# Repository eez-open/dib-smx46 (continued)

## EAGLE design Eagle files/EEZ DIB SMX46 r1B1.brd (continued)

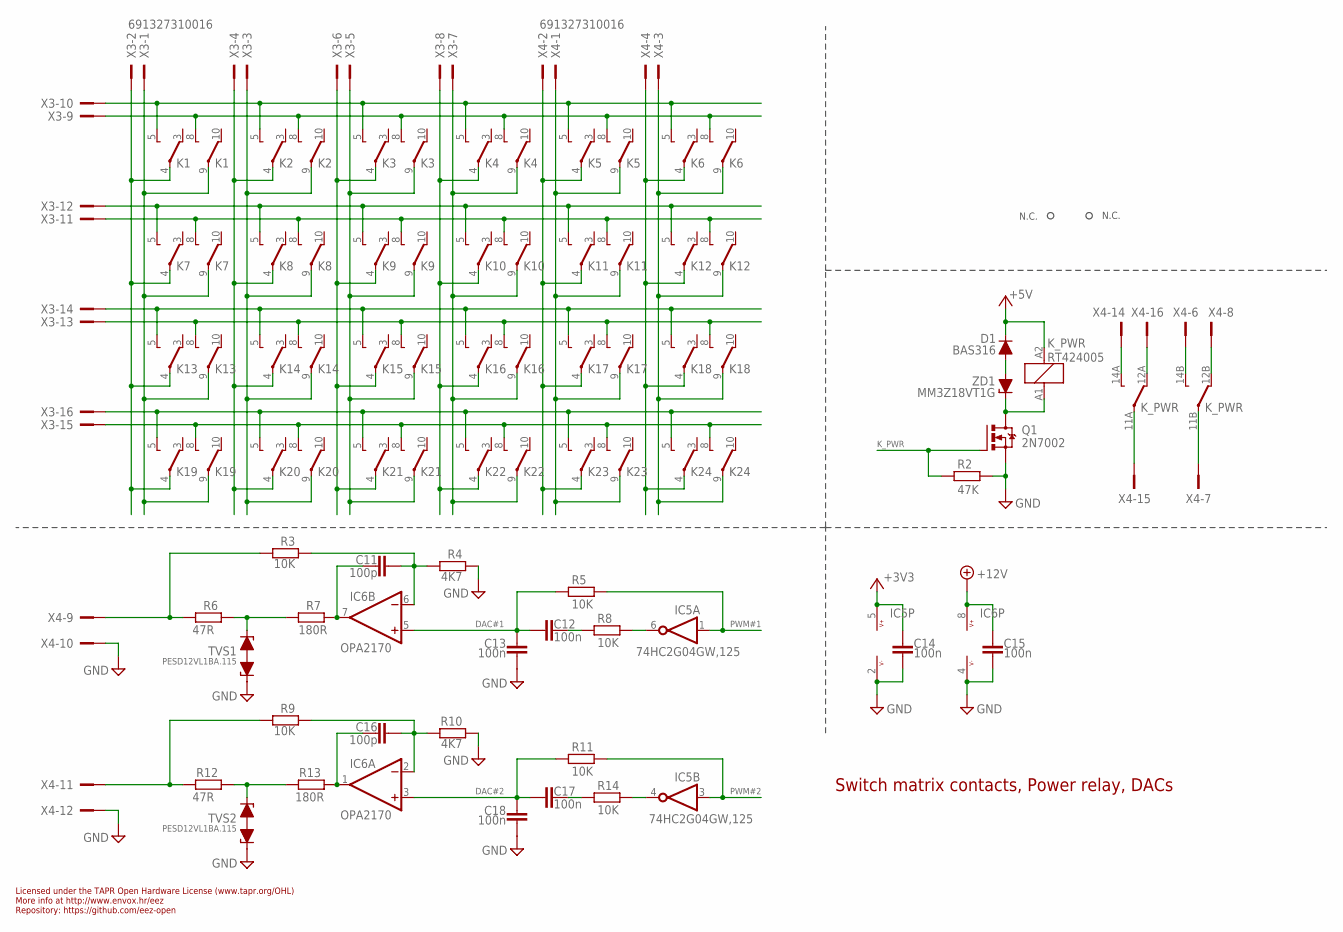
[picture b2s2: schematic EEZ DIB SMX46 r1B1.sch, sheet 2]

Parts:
C11, C16: 100p; C0805
C12, C13, C14, C15, C17, C18: 100n; C0603
D1: BAS316; SOD323-R
IC5: 74HC2G04GW,125; SOT65P210X110-6N
IC6: OPA2170; SOIC127P600X173-8N
K1, K2, K3, K4, K5, K6, K7, K8, K9, K10, K11, K12, K13, K14, K15, K16, K17, K18, K19, K20, K21, K22, K23, K24: FTR-C1GA012G-B05; FTR-C1
K_PWR: RT424005; RT-C/016A5_ROUND
Q1: 2N7002; SOT103P240X110-3N; MPN 2N7002-7-F
R2: 47K; R0805
R3, R5, R8, R9, R11, R14: 10K; R0805
R4, R10: 4K7; R0805
R6, R12: 47R; R0805
R7, R13: 180R; R0805
TVS1, TVS2: PESD12VL1BA.115; SOD323-BIDIR
X3, X4: 691327310016
ZD1: MM3Z18VT1G; SOD323-R

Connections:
+3V3: C14.1, IC5.5 (V+); also elsewhere on the board
+5V: D1.C, K_PWR.A2 (C1); also elsewhere on the board
+12V: C15.1, IC6.8 (V+); also elsewhere on the board
DAC#1: C12.1, C13.1, IC6.5 (+IN), R5.1
DAC#2: C17.1, C18.1, IC6.3 (+IN), R11.1
GND: C13.2, C14.2, C15.2, C18.2, IC5.2 (V-), IC6.4 (V-), Q1.2 (S), R2.1, R4.1, R10.1, TVS1.1, TVS2.1, X4.10, X4.12; also elsewhere on the board
ISET1: R6.1, R7.2, TVS1.2
ISET2: R12.1, R13.2, TVS2.2
K_PWR: Q1.1 (G), R2.2; also elsewhere on the board
unnamed: K1.4, K7.4, K13.4, K19.4, X3.2
unnamed: K1.9, K7.9, K13.9, K19.9, X3.1
unnamed: K13.5 (O), K14.5 (O), K15.5 (O), K16.5 (O), K17.5 (O), K18.5 (O), X3.14
unnamed: K13.8 (O), K14.8 (O), K15.8 (O), K16.8 (O), K17.8 (O), K18.8 (O), X3.13
unnamed: K7.5 (O), K8.5 (O), K9.5 (O), K10.5 (O), K11.5 (O), K12.5 (O), X3.12
unnamed: K7.8 (O), K8.8 (O), K9.8 (O), K10.8 (O), K11.8 (O), K12.8 (O), X3.11
unnamed: K19.5 (O), K20.5 (O), K21.5 (O), K22.5 (O), K23.5 (O), K24.5 (O), X3.16
unnamed: K19.8 (O), K20.8 (O), K21.8 (O), K22.8 (O), K23.8 (O), K24.8 (O), X3.15
unnamed: K5.4, K11.4, K17.4, K23.4, X4.2
unnamed: K2.4, K8.4, K14.4, K20.4, X3.4
unnamed: K2.9, K8.9, K14.9, K20.9, X3.3
unnamed: K5.9, K11.9, K17.9, K23.9, X4.1
unnamed: K6.4, K12.4, K18.4, K24.4, X4.4
unnamed: K6.9, K12.9, K18.9, K24.9, X4.3
unnamed: K3.4, K9.4, K15.4, K21.4, X3.6
unnamed: K3.9, K9.9, K15.9, K21.9, X3.5
unnamed: K4.4, K10.4, K16.4, K22.4, X3.8
unnamed: K4.9, K10.9, K16.9, K22.9, X3.7
unnamed: R3.2, R6.2, X4.9
unnamed: C17.2, R14.1
unnamed: IC5.4 (O), R14.2
unnamed: C11.1, IC6.7 (OUT), R7.1
unnamed: C16.2, IC6.2 (-IN), R9.1, R10.2
unnamed: C16.1, IC6.1 (OUT), R13.1
unnamed: K1.5 (O), K2.5 (O), K3.5 (O), K4.5 (O), K5.5 (O), K6.5 (O), X3.10
unnamed: K1.8 (O), K2.8 (O), K3.8 (O), K4.8 (O), K5.8 (O), K6.8 (O), X3.9
unnamed: K_PWR.11B, X4.7
unnamed: K_PWR.12B (S), X4.8
unnamed: R9.2, R12.2, X4.11
unnamed: K_PWR.14B (O), X4.6
unnamed: K_PWR.11A, X4.15
unnamed: K_PWR.12A (S), X4.16
unnamed: K_PWR.14A (O), X4.14
unnamed: D1.A, ZD1.A
unnamed: K_PWR.A1 (C2), Q1.3 (D), ZD1.C
unnamed: C12.2, R8.1
unnamed: C11.2, IC6.6 (-IN), R3.1, R4.2
unnamed: IC5.6 (O), R8.2
PWM#1: IC5.1 (I), R5.2; also elsewhere on the board
PWM#2: IC5.3 (I), R11.2; also elsewhere on the board

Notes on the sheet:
Licensed under the TAPR Open Hardware License (www.tapr.org/OHL)
Repository: https://github.com/eez-open
More info at http://www.envox.hr/eez
Switch matrix contacts, Power relay, DACs
N.C.

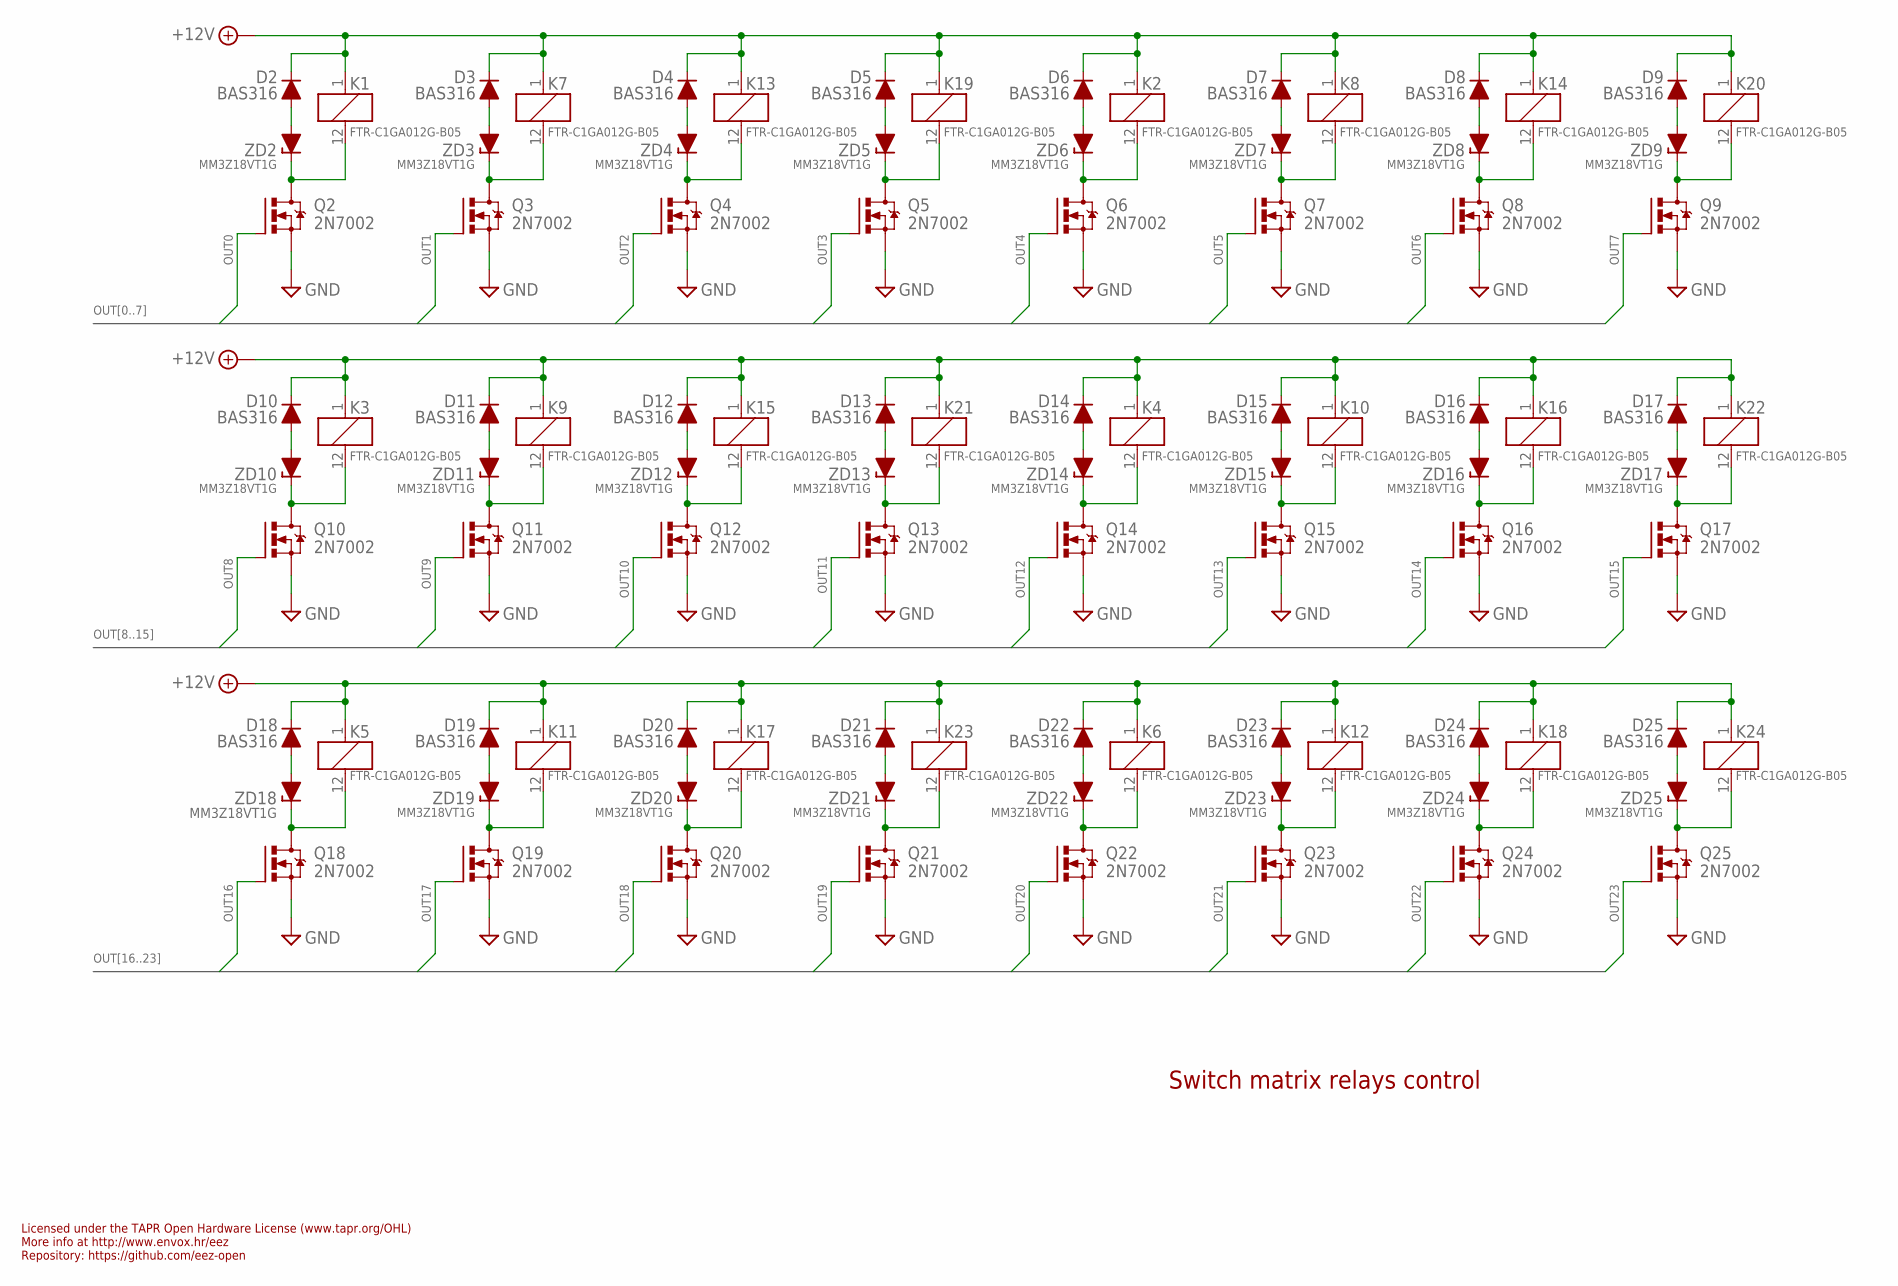
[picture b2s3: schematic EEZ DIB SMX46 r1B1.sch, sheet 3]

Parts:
D2, D3, D4, D5, D6, D7, D8, D9, D10, D11, D12, D13, D14, D15, D16, D17, D18, D19, D20, D21, D22, D23, D24, D25: BAS316; SOD323-R
K1, K2, K3, K4, K5, K6, K7, K8, K9, K10, K11, K12, K13, K14, K15, K16, K17, K18, K19, K20, K21, K22, K23, K24: FTR-C1GA012G-B05; FTR-C1
Q2, Q3, Q4, Q5, Q6, Q7, Q8, Q9, Q10, Q11, Q12, Q13, Q14, Q15, Q16, Q17, Q18, Q19, Q20, Q21, Q22, Q23, Q24, Q25: 2N7002; SOT103P240X110-3N; MPN 2N7002-7-F
ZD2, ZD3, ZD4, ZD5, ZD6, ZD7, ZD8, ZD9, ZD10, ZD11, ZD12, ZD13, ZD14, ZD15, ZD16, ZD17, ZD18, ZD19, ZD20, ZD21, ZD22, ZD23, ZD24, ZD25: MM3Z18VT1G; SOD323-R

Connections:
+12V: D2.C, D3.C, D4.C, D5.C, D6.C, D7.C, D8.C, D9.C, D10.C, D11.C, D12.C, D13.C, D14.C, D15.C, D16.C, D17.C, D18.C, D19.C, D20.C, D21.C, D22.C, D23.C, D24.C, D25.C, K1.1 (C1), K2.1 (C1), K3.1 (C1), K4.1 (C1), K5.1 (C1), K6.1 (C1), K7.1 (C1), K8.1 (C1), K9.1 (C1), K10.1 (C1), K11.1 (C1), K12.1 (C1), K13.1 (C1), K14.1 (C1), K15.1 (C1), K16.1 (C1), K17.1 (C1), K18.1 (C1), K19.1 (C1), K20.1 (C1), K21.1 (C1), K22.1 (C1), K23.1 (C1), K24.1 (C1); also elsewhere on the board
GND: Q2.2 (S), Q3.2 (S), Q4.2 (S), Q5.2 (S), Q6.2 (S), Q7.2 (S), Q8.2 (S), Q9.2 (S), Q10.2 (S), Q11.2 (S), Q12.2 (S), Q13.2 (S), Q14.2 (S), Q15.2 (S), Q16.2 (S), Q17.2 (S), Q18.2 (S), Q19.2 (S), Q20.2 (S), Q21.2 (S), Q22.2 (S), Q23.2 (S), Q24.2 (S), Q25.2 (S); also elsewhere on the board
unnamed: D4.A, ZD4.A
unnamed: K13.12 (C2), Q4.3 (D), ZD4.C
unnamed: D10.A, ZD10.A
unnamed: D8.A, ZD8.A
unnamed: K14.12 (C2), Q8.3 (D), ZD8.C
unnamed: K3.12 (C2), Q10.3 (D), ZD10.C
unnamed: D9.A, ZD9.A
unnamed: K20.12 (C2), Q9.3 (D), ZD9.C
unnamed: D11.A, ZD11.A
unnamed: K9.12 (C2), Q11.3 (D), ZD11.C
unnamed: D7.A, ZD7.A
unnamed: K8.12 (C2), Q7.3 (D), ZD7.C
unnamed: D12.A, ZD12.A
unnamed: K15.12 (C2), Q12.3 (D), ZD12.C
unnamed: D6.A, ZD6.A
unnamed: K2.12 (C2), Q6.3 (D), ZD6.C
unnamed: D13.A, ZD13.A
unnamed: K21.12 (C2), Q13.3 (D), ZD13.C
unnamed: D3.A, ZD3.A
unnamed: K7.12 (C2), Q3.3 (D), ZD3.C
unnamed: D14.A, ZD14.A
unnamed: K4.12 (C2), Q14.3 (D), ZD14.C
unnamed: D2.A, ZD2.A
unnamed: K1.12 (C2), Q2.3 (D), ZD2.C
unnamed: D15.A, ZD15.A
unnamed: K10.12 (C2), Q15.3 (D), ZD15.C
unnamed: D5.A, ZD5.A
unnamed: K19.12 (C2), Q5.3 (D), ZD5.C
unnamed: D16.A, ZD16.A
unnamed: K16.12 (C2), Q16.3 (D), ZD16.C
unnamed: D17.A, ZD17.A
unnamed: K22.12 (C2), Q17.3 (D), ZD17.C
unnamed: D19.A, ZD19.A
unnamed: K11.12 (C2), Q19.3 (D), ZD19.C
unnamed: D20.A, ZD20.A
unnamed: K17.12 (C2), Q20.3 (D), ZD20.C
unnamed: D21.A, ZD21.A
unnamed: K23.12 (C2), Q21.3 (D), ZD21.C
unnamed: D22.A, ZD22.A
unnamed: K6.12 (C2), Q22.3 (D), ZD22.C
unnamed: D23.A, ZD23.A
unnamed: K12.12 (C2), Q23.3 (D), ZD23.C
unnamed: D18.A, ZD18.A
unnamed: K5.12 (C2), Q18.3 (D), ZD18.C
unnamed: D24.A, ZD24.A
unnamed: K18.12 (C2), Q24.3 (D), ZD24.C
unnamed: D25.A, ZD25.A
unnamed: K24.12 (C2), Q25.3 (D), ZD25.C
OUT0: Q2.1 (G); also elsewhere on the board
OUT1: Q3.1 (G); also elsewhere on the board
OUT2: Q4.1 (G); also elsewhere on the board
OUT3: Q5.1 (G); also elsewhere on the board
OUT4: Q6.1 (G); also elsewhere on the board
OUT5: Q7.1 (G); also elsewhere on the board
OUT6: Q8.1 (G); also elsewhere on the board
OUT7: Q9.1 (G); also elsewhere on the board
OUT8: Q10.1 (G); also elsewhere on the board
OUT9: Q11.1 (G); also elsewhere on the board
OUT10: Q12.1 (G); also elsewhere on the board
OUT11: Q13.1 (G); also elsewhere on the board
OUT12: Q14.1 (G); also elsewhere on the board
OUT13: Q15.1 (G); also elsewhere on the board
OUT14: Q16.1 (G); also elsewhere on the board
OUT15: Q17.1 (G); also elsewhere on the board
OUT16: Q18.1 (G); also elsewhere on the board
OUT17: Q19.1 (G); also elsewhere on the board
OUT18: Q20.1 (G); also elsewhere on the board
OUT19: Q21.1 (G); also elsewhere on the board
OUT20: Q22.1 (G); also elsewhere on the board
OUT21: Q23.1 (G); also elsewhere on the board
OUT22: Q24.1 (G); also elsewhere on the board
OUT23: Q25.1 (G); also elsewhere on the board

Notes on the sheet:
Licensed under the TAPR Open Hardware License (www.tapr.org/OHL)
Repository: https://github.com/eez-open
More info at http://www.envox.hr/eez
Switch matrix relays control

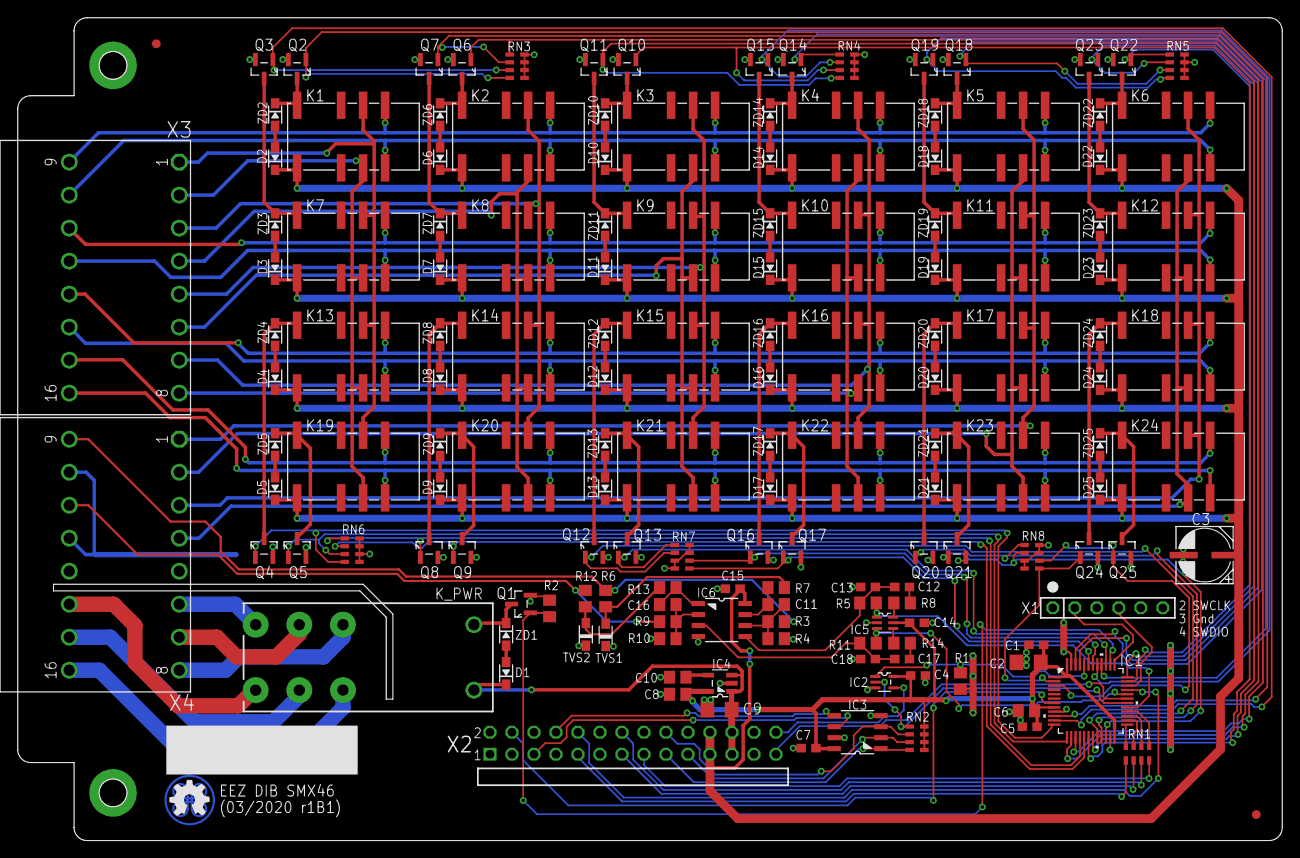
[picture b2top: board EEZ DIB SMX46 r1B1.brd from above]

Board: 2 copper layers, 146.0 x 95.0 mm, 157 parts (0 on the bottom side), 143 nets.

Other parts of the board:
EEZ_SIGNATURE: SIGNATURESMALL; SIGNATURE_5MM

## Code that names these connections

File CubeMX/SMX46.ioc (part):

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Mcu.Name=STM32F030C6Tx
Mcu.Package=LQFP48
Mcu.UserName=STM32F030C6Tx
PA0.GPIOParameters=GPIO_Label
PA0.GPIO_Label=OUT0
PA0.Signal=GPIO_Output
PA1.GPIOParameters=GPIO_Label
PA1.GPIO_Label=OUT1
PA1.Signal=GPIO_Output
PA10.Mode=Asynchronous
PA10.Signal=USART1_RX
PA11.GPIOParameters=GPIO_Label
PA11.GPIO_Label=PWM2
PA11.Signal=S_TIM1_CH4
PA12.GPIOParameters=GPIO_Label
PA12.GPIO_Label=DIB_IRQ
PA12.Signal=GPIO_Output
PA13.Mode=Serial_Wire
PA13.Signal=SYS_SWDIO
PA14.Mode=Serial_Wire
PA14.Signal=SYS_SWCLK
PA15.GPIOParameters=GPIO_Label
PA15.GPIO_Label=K_PWR
PA15.Signal=GPIO_Output
PA2.GPIOParameters=GPIO_Label
PA2.GPIO_Label=OUT2
PA2.Signal=GPIO_Output
PA3.GPIOParameters=GPIO_Label
PA3.GPIO_Label=OUT3
PA3.Signal=GPIO_Output
PA4.GPIOParameters=GPIO_Label
PA4.GPIO_Label=OUT4
PA4.Signal=GPIO_Output
PA5.GPIOParameters=GPIO_Label
PA5.GPIO_Label=OUT5
PA5.Signal=GPIO_Output
PA6.GPIOParameters=GPIO_Label
PA6.GPIO_Label=OUT6
PA6.Signal=GPIO_Output
PA7.GPIOParameters=GPIO_Label
PA7.GPIO_Label=OUT7
PA7.Signal=GPIO_Output
PA8.GPIOParameters=GPIO_Label
PA8.GPIO_Label=PWM1
PA8.Signal=S_TIM1_CH1
PA9.Mode=Asynchronous
PA9.Signal=USART1_TX
PB0.GPIOParameters=GPIO_Label
PB0.GPIO_Label=OUT8
PB0.Signal=GPIO_Output
PB1.GPIOParameters=GPIO_Label
PB1.GPIO_Label=OUT9
PB1.Signal=GPIO_Output
PB10.GPIOParameters=GPIO_Label
PB10.GPIO_Label=OUT18
PB10.Signal=GPIO_Output
PB11.GPIOParameters=GPIO_Label
PB11.GPIO_Label=OUT19
PB11.Signal=GPIO_Output
PB12.GPIOParameters=GPIO_Label
PB12.GPIO_Label=DIB_CSA
PB12.Mode=NSS_Signal_Hard_Input
PB12.Signal=SPI1_NSS
PB13.GPIOParameters=GPIO_Label
PB13.GPIO_Label=DIB_SCLK
PB13.Mode=Full_Duplex_Slave
PB13.Signal=SPI1_SCK
PB14.GPIOParameters=GPIO_Label
PB14.GPIO_Label=DIB_MISO
PB14.Mode=Full_Duplex_Slave
PB14.Signal=SPI1_MISO
PB15.GPIOParameters=GPIO_Label
PB15.GPIO_Label=DIB_MOSI
PB15.Mode=Full_Duplex_Slave
PB15.Signal=SPI1_MOSI
PB2.GPIOParameters=GPIO_Label
PB2.GPIO_Label=OUT10
PB2.Signal=GPIO_Output
PB3.GPIOParameters=GPIO_Label
PB3.GPIO_Label=OUT11
PB3.Signal=GPIO_Output
PB4.GPIOParameters=GPIO_Label
PB4.GPIO_Label=OUT12
PB4.Signal=GPIO_Output
PB5.GPIOParameters=GPIO_Label
PB5.GPIO_Label=OUT13
PB5.Signal=GPIO_Output
PB6.GPIOParameters=GPIO_Label
PB6.GPIO_Label=OUT14
PB6.Signal=GPIO_Output
PB7.GPIOParameters=GPIO_Label
PB7.GPIO_Label=OUT15
PB7.Signal=GPIO_Output
PB8.GPIOParameters=GPIO_Label
PB8.GPIO_Label=OUT16
PB8.Signal=GPIO_Output
PB9.GPIOParameters=GPIO_Label
PB9.GPIO_Label=OUT17
PB9.Signal=GPIO_Output
PC13.GPIOParameters=GPIO_Label
PC13.GPIO_Label=OUT22
PC13.Signal=GPIO_Output
PC14-OSC32_IN.GPIOParameters=GPIO_Label
PC14-OSC32_IN.GPIO_Label=OUT23
PC14-OSC32_IN.Signal=GPIO_Output
PC15-OSC32_OUT.GPIOParameters=GPIO_Label
PC15-OSC32_OUT.GPIO_Label=DIB_SYNC
PC15-OSC32_OUT.Signal=GPIO_Input
PF6.GPIOParameters=GPIO_Label
PF6.GPIO_Label=OUT20
PF6.Signal=GPIO_Output
PF7.GPIOParameters=GPIO_Label
PF7.GPIO_Label=OUT21
PF7.Signal=GPIO_Output
board=custom

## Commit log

2020-02-14 readme.me update
2020-02-15 Eagle files added
2020-02-15 MCU .ioc file
2020-02-22 UART relocated
2020-02-26 debug connector update
2020-02-28 PCB terminals position adjusted
2020-02-29 IC2 package update
2020-03-19 front panel connectors position adjusted
2020-04-06 #1, #2 fixed
2020-05-04 swap UART TX and RX
2020-05-18 prototype picture
2020-06-12 DIB alternative IRQs added
2020-09-19 BOM added
2020-09-20 schematics update
2020-09-20 front panel labels update
2020-09-20 Gerbers update
2020-09-20 C6 value
2020-10-08 Update schematics pdf
2020-10-25 prototype r1B2 picture
2020-12-02 #4, OSHW UID
2020-12-02 #5, BOM update
2020-12-02 Gerbers updatereadme.md
2020-12-13 ADIB ID=001
2020-12-13 added link to firmware repository
2020-12-21 RN2 value update
2021-01-16 r1B5 prototype picture
2021-01-30 PCB ID added
2021-01-31 BOM update
2021-03-25 BOM header date fix
2021-03-25 Module front mask
2021-03-25 Centroid files
